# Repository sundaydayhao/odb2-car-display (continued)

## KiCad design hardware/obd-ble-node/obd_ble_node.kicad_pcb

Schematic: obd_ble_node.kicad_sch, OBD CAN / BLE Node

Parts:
AE1: AANI-CH-0133-Q; AANI-CH-0133-Q_Corner; MPN AANI-CH-0133-Q-T
C1: 2.2u 50V; C_0805_2012Metric; MPN GRM21BR71H225KA12L
C2: 100n 50V; C_0402_1005Metric; MPN GRM155R71H104KE14D
C3: 100n 16V; C_0402_1005Metric; MPN 100n 16V
C4, C5: 10u 25V; C_0805_2012Metric; MPN GRM21BR61E106KA73L
C6: 2.2u 10V; C_0402_1005Metric; MPN 2.2u 10V
C7, C11: 10u 10V; C_0603_1608Metric; MPN 10u 10V
C8, C9, C10, C12, C13, C14, C15, C22: 100n; C_0402_1005Metric; MPN 100n
C16, C17: 1u; C_0402_1005Metric; MPN 1u
C18, C19: 16p C0G; C_0402_1005Metric; MPN 16p C0G
C20, C21: 1.5p C0G; C_0201_0603Metric; MPN 1.5p C0G
C23: DNP / ANT TUNE; C_0402_1005Metric; MPN DNP / ANT TUNE; not fitted
D1: SS110 100V; D_SMA; MPN SS110
D2: SMBJ18A; D_SMB; MPN SMBJ18A
D3: PESD2CANFD24V-T; SOT-23; MPN PESD2CANFD24V-T
D4: GREEN; LED_0402_1005Metric; MPN GREEN
F1: 500mA 63V; Fuse_1206_3216Metric; MPN 0466.500NR
FB1: 600R@100M 500mA; L_0402_1005Metric; MPN BLM15AG601SN1D
H1: D1.2 NPTH; Fixture_Round_D1.2mm; MPN D1.2 NPTH
H2: 1.6x1.2 NPTH; Fixture_Slot_1.6x1.2mm; MPN 1.6x1.2 NPTH
J1: OBD-II 16P / STRAIGHT TAIL ASSUMPTION; OBD_StraightTail_16P_4x8p6_Assumed; MPN OBD-II 16P / STRAIGHT TAIL ASSUMPTION
L1: 10uH >=3A Isat; L_Coilcraft_XAL4030-XXX; MPN XGL4030-103MEC
L2: 2.4nH; L_0201_0603Metric; MPN LQP03TG2N4B02D
L3: 5.6nH TUNE; L_0402_1005Metric; MPN LQW15AN5N6C10
L4: 1.8nH TUNE; L_0402_1005Metric; MPN LQW15AN1N8C00
R1: 84.5k 1%; R_0402_1005Metric; MPN 84.5k 1%
R2: 16.2k 1%; R_0402_1005Metric; MPN 16.2k 1%
R3, R4, R5, R6, R7, R8: 10k; R_0402_1005Metric; MPN 10k
R9: 1M 1%; R_0402_1005Metric; MPN 1M 1%
R10: 100k 1%; R_0402_1005Metric; MPN 100k 1%
R11: 1k; R_0402_1005Metric; MPN 1k
R12: 499R; R_0402_1005Metric; MPN 499R
TP1: GND; TestPoint_Pad_D1.0mm; MPN GND
TP2: +3V3; TestPoint_Pad_D1.0mm; MPN +3V3
TP3: EN; TestPoint_Pad_D1.0mm; MPN EN
TP4: BOOT; TestPoint_Pad_D1.0mm; MPN BOOT
TP5: U0RX; TestPoint_Pad_D1.0mm; MPN U0RX
TP6: UART_TX; TestPoint_Pad_D1.0mm; MPN UART_TX
TP7: USB_DM; TestPoint_Pad_D1.0mm; MPN USB_DM
TP8: USB_DP; TestPoint_Pad_D1.0mm; MPN USB_DP
TP9: +5V; TestPoint_Pad_D1.0mm; MPN +5V
U1: LMR51610YDBVR; SOT-23-6; MPN LMR51610YDBVR
U2: TLV75533PDBVR; SOT-23-5; MPN TLV75533PDBVR
U3: TCAN1044AVDRBRQ1; VSON-8-1EP_3x3mm_P0.65mm_EP1.65x2.4mm; MPN TCAN1044AVDRBRQ1
U4: SN74LVC1G32DCKR; SOT-353_SC-70-5; MPN SN74LVC1G32DCKR
U5: ESP32-C3FH4X; QFN-32-1EP_5x5mm_P0.5mm_EP3.7x3.7mm; MPN ESP32-C3FH4X
Y1: 40MHz CL=10pF; Crystal_SMD_3225-4Pin_3.2x2.5mm; MPN ABM8G-40.000MHZ-10-D2X-T

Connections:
/+3V3: C7.1, C9.1, C10.1, C13.1, C14.1, C15.1, FB1.1, R3.1, R4.1, R5.1, R6.1, R7.1, R8.1, TP2.1, U2.5 (OUT), U3.5 (VIO), U4.5 (VCC), U5.11 (VDD3P3_RTC), U5.17 (VDD3P3_CPU), U5.31 (VDDA_1), U5.32 (VDDA_2)
/+5V: C4.1, C5.1, C6.1, C8.1, L1.2, R1.1, TP9.1, U2.1 (IN), U2.3 (EN), U3.3 (VCC)
/ANT_FEED: AE1.1 (RF_FEED), C23.1, L3.2
/BOOT: R8.2, TP4.1, U5.15 (GPIO9 / BOOT)
/BOOT_SW: C3.1, U1.1 (CB)
/CAN_H: D3.2 (CANH), J1.6 (OBD_6), U3.7 (CANH)
/CAN_L: D3.1 (CANL), J1.14 (OBD_14), U3.6 (CANL)
/CAN_RX: U3.4 (RXD), U5.8 (GPIO3 / CAN_RX)
/CAN_STB: R4.2, U3.8 (STB), U5.10 (GPIO5 / CAN_STB)
/CAN_TX: U4.1 (A), U5.5 (GPIO1 / CAN_TX)
/EN: C17.1, R5.2, TP3.1, U5.7 (CHIP_EN)
/FB5: R1.2, R2.1, U1.3 (FB)
/GND: C1.2, C2.2, C4.2, C5.2, C6.2, C7.2, C8.2, C9.2, C10.2, C11.2, C12.2, C13.2, C14.2, C15.2, C16.2, C17.2, C18.2, C19.2, C20.2, C21.2, C22.2, C23.2, D2.2 (A2), D3.3 (GND), D4.1 (K), J1.4 (OBD_4), J1.5 (OBD_5), L4.2, R2.2, R10.2, TP1.1, U1.2 (GND), U2.2 (GND), U3.2 (GND), U3.9 (EP), U4.3 (GND), U5.33 (EP_GND), Y1.2 (G), Y1.4 (G)
/LED: R11.1, U5.12 (GPIO6 / LED)
/LED_A: D4.2 (A), R11.2
/RF50: C21.1, L2.2, L3.1, L4.1
/RF_SOC: C20.1, L2.1, U5.1 (LNA_IN)
/STRAP2: R6.2, U5.6 (GPIO2 / STRAP)
/STRAP8: R7.2, U5.14 (GPIO8 / STRAP)
/SW: C3.2, L1.1, U1.6 (SW)
/TXD_GATE: U3.1 (TXD), U4.4 (Y)
/TX_INHIBIT: R3.2, U4.2 (B), U5.9 (GPIO4 / TX_INHIBIT)
/U0RX: TP5.1, U5.27 (GPIO20 / U0RXD)
/U0TX: R12.1, U5.28 (GPIO21 / U0TXD)
/UART_TX: R12.2, TP6.1
/USB_DM: TP7.1, U5.25 (GPIO18 / USB_D-)
/USB_DP: TP8.1, U5.26 (GPIO19 / USB_D+)
/VBAT: F1.1, J1.16 (OBD_16)
/VBAT_ADC: C22.1, R9.2, R10.1, U5.4 (GPIO0 / ADC1_CH0)
/VBAT_FUSED: D1.2 (A), F1.2
/VDD_RF: C11.1, C12.1, FB1.2, U5.2 (VDD3P3_1), U5.3 (VDD3P3_2)
/VDD_SPI: C16.1, U5.18 (VDD_SPI)
/VIN_PROT: C1.1, C2.1, D1.1 (K), D2.1 (A1), R9.1, U1.4 (EN), U1.5 (VIN)
/XTAL_N: C19.1, U5.29 (XTAL_N), Y1.3
/XTAL_P: C18.1, U5.30 (XTAL_P), Y1.1

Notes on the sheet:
REV A3 / 38.5 x 16.6 mm / CAN + BLE / GROUPED TEST PADS + FIXTURE DATUMS
J1: straight-tail 4.00 x 8.60 mm grid ASSUMED Plated slot 2.40 x 1.20 mm: verify actual plug fit.
12 V INPUT / REVERSE PROTECTION / 65 V BUCK / 5 V -> 3.3 V
No 120 ohm termination on vehicle stub. TX inhibit HIGH physically forces recessive.
RESET / STRAPS / 40 MHz
C3FH4X: integrated flash, pins 19..24 NC. VDD_SPI is a supply output.
RF / 50 ohm reference plane / match values require VNA tuning in final case
ADC senses VIN_PROT; fuse and diode drop are not compensated.
USB pads: DATA ONLY. Fixture power requires vehicle disconnection.

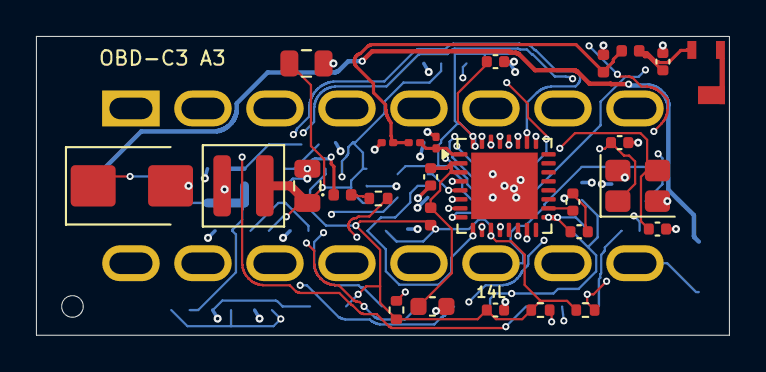
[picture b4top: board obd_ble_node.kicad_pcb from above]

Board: 4 copper layers, 38.5 x 16.6 mm, 64 parts (34 on the bottom side), 35 nets.

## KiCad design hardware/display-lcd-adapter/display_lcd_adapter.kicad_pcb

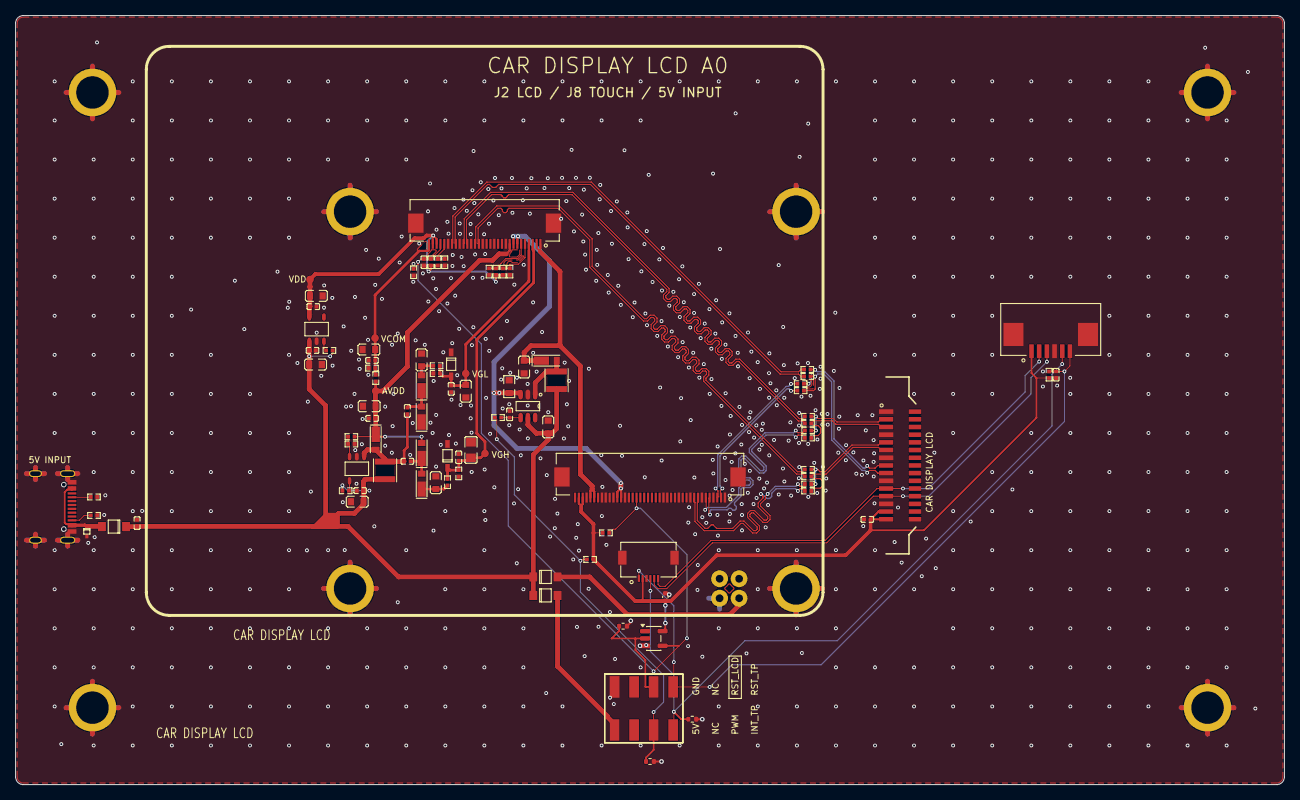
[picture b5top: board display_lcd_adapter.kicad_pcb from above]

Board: 2 copper layers, 165.0 x 100.0 mm, 108 parts (0 on the bottom side), 53 nets.

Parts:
C1: 1u / 16V; C0402__b328da3f93
C2: 1u/16V; C0402__b328da3f93
C3, C8, C9, C11, C13, C15, C16, C22, C24, C25, C26: 0.1u/50V; C0402__b328da3f93
C4, C5, C7, C10, C12, C14, C21, C27: 10u/25V; C0603__4affcd651d
C6: 22p/50V; C0402__b328da3f93
C17, C18: 1u/50V; C0603__4affcd651d
C23: 10u/50V; C0805__9959ce48b0
C28: 100n / 16V; C_0402_1005Metric__56c42d4718
D1, D3, D12: DSS24; SOD123FL__46ae4cb21a
D2: LESD5D5.0CT1G; SOD523__04fef8a58b
D4, D5, D6, D7, D8, D9: LMBR140ET1G; SOD323HE__f9a9ee848d
D10: LMSZ5233BT1G; SOD123__b888afbd6d
D11: MM1W18; SOD123__b888afbd6d
H1, H2, H3, H4, H5, H6, H7, H8: STD; HOLE6P2_4P22__65e4372978
J1: USB_TYPEC_16P_F; USB_TYPEC_16P_F__86066a2b25
J2: LCD_30P_0.5mm; FFC30P_0P5__db095f96ca
J3: DSI_15P_1mm; FFC_15P_1_MIPI__6610367bd7
J5: FPC_6P_1mm_UNUSED; FFC6P_1_UP__634cfe9cbb
J6: AUX_5V_BL_RESET_TOUCH; CON4X2_2P54_SMT__7e2a9205d1
J7: FPC_40P_UNUSED; FFC40P_0P5__8d5a270b71
J8: GT911_6P_0.5mm; FFC6P_0P5_UP__fd49314884
L1, L2: 10uH_0.8A; L3012S__5941442135
R1, R2, R3, R4, R5, R6, R7, R10, R11, R13, R14, R24, R38: 10k; R0402__b308b0f41e
R8, R9: 5.1k; R0402__b308b0f41e
R12: 1.1; R0603__10d1fcc181
R15: 22k; R0402__b308b0f41e
R16: 3.3k; R0402__b308b0f41e
R17, R18: 220; R0402__b308b0f41e
R19, R20: 51k; R0402__b308b0f41e
R22, R37: 1k; R0402__b308b0f41e
R23: 2k; R0402__b308b0f41e
R25, R26, R27, R28, R29, R30: 0; R0402__b308b0f41e
R31, R32, R33, R34, R35, R36: 0R; R0402__b308b0f41e
R39, R41: 10k; R_0402_1005Metric__e20e110129
R40: 100k; R_0402_1005Metric__e20e110129
TP1, TP2, TP3, TP4: TEST; TPC1__3c95fc0e3d
TP5: TEST; TPC1__999ff27256
TP6, TP7, TP8, TP9: TEST; HOLE2P2_1__191d9da361
U1: ETA1611; SOT23-6__2edaa2116b
U2: ME6211C18M5G-N; SOT23-5__5f716075cd
U3: AP3012k; SOT23-5__5f716075cd
U4: SN74LVC1G07DBVR; SOT-23-5__81a06d98de

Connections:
A_CLKN: J2.18, R27.1
A_CLKP: J2.17, R28.1
A_DATN0: J2.24, R29.1
A_DATN1: J2.21, R25.1
A_DATP0: J2.23, R30.1
A_DATP1: J2.20, R26.1
B_CLKN: J7.9, R33.1
B_CLKP: J7.8, R34.1
B_DATN0: J7.3, R35.1
B_DATN1: J7.6, R31.1
B_DATP0: J7.2, R36.1
B_DATP1: J7.5, R32.1
ESP32_CLKN: J3.5, R27.2, R33.2
ESP32_CLKP: J3.6, R28.2, R34.2
ESP32_DATN0: J3.8, R29.2, R35.2
ESP32_DATN1: J3.2, R25.2, R31.2
ESP32_DATP0: J3.9, R30.2, R36.2
ESP32_DATP1: J3.3, R26.2, R32.2
ESP32_I2C_SCL: J3.11, J5.2, J8.6
ESP32_I2C_SDA: J3.12, J5.3, J8.5
GND: C1.2, C2.2, C3.2, C4.2, C5.2, C6.2, C7.2, C8.2, C9.2, C10.2, C11.2, C12.2, C13.2, C14.2, C17.2, C18.2, C21.2, C22.2, C23.2, C24.2, C25.2, C26.2, C27.2, C28.2, D2.1, D8.2, D10.2, D11.1, H1.1, H2.1, H3.1, H4.1, H5.1, H6.1, H7.1, H8.1, J1.1, J1.2, J1.15, J1.16, J1.17, J1.18, J1.19, J1.20, J2.10, J2.13, J2.16, J2.19, J2.22, J2.25, J2.31, J2.32, J3.1, J3.4, J3.7, J3.10, J3.13, J5.4, J5.7, J5.8, J6.2, J7.1, J7.4, J7.7, J7.10, J7.13, J7.16, J7.17, J7.27, J7.30, J7.32, J7.33, J7.37, J7.41, J7.42, J8.3, J8.7, J8.8, R5.1, R6.1, R7.1, R8.1, R9.1, R12.1, R16.2, R19.1, R20.1, R22.1, R38.1, R39.2, R40.2, R41.2, TP7.1, U1.2, U2.2, U3.2, U4.3
INT_TP: J5.5, J6.7, J8.4, R40.1
LCD_AVDD: C13.1, C14.1, D5.2, D6.1, J2.9, R15.1, R23.2, TP4.1
LCD_RESET_HOST: J6.6, R39.1, U4.2
LCD_VCOM: C26.1, C27.1, J2.30, R22.2, R23.1, TP3.1
LCD_VDD: C9.1, C10.1, J2.28, J2.29, R1.2, R2.2, R3.2, R4.2, TP5.1, U2.5
LCD_VGH: C23.1, C24.1, D11.2, J2.3, R18.2, R20.2, TP2.1
LCD_VGL: C21.1, C22.1, D10.1, J2.4, R17.2, R19.2, TP1.1
LED+: C5.1, D4.2, J2.1, J2.2, J7.35, J7.36
LED-: J2.7, J2.8, J7.28, J7.29, R12.2, U1.3
LED_CTRL: J6.5, R11.2, R24.1, R41.1
N17127832: D4.1, L1.2, U1.1
N17127878: C6.1, R11.1, U1.4
N17128822: R13.1, U2.3
N17131715: J1.6, R8.2
N17131721: J1.12, R9.2
N17132617: D3.1, J6.1
N17134769: R14.1, U3.4
N17134948: C15.2, C16.2, D5.1, L2.2, U3.1
N17135258: R15.2, R16.1, U3.3
N17135942: C16.1, D8.1, D9.2
N17136021: C15.1, D6.2, D7.1
N17136250: C18.1, D7.2, R18.1
N17136498: C17.1, D9.1, R17.1
N17147084: D12.1, TP6.1
RESET_LCD: C1.1, J2.27, J7.24, R4.1, R37.1, R38.2, U4.4
RESET_TP: C2.1, J5.6, J6.8, J8.1, R10.1
SHLR: J2.6, R2.1, R6.2
STBYB: J2.26, R3.1, R7.2
UPDN: J2.5, R1.1, R5.2
USB_5V: D1.1, D2.2, J1.3, J1.4, J1.13, J1.14
VCC_5V: C4.1, C7.1, C8.1, C11.1, C12.1, C25.1, D1.2, D3.2, D12.2, L1.1, L2.1, R13.2, R14.2, U1.5, U2.1, U3.5
VDD_3V3: C3.1, C28.1, J3.14, J3.15, J5.1, J7.38, J7.39, J8.2, R10.2, R24.2, R37.2, U4.5

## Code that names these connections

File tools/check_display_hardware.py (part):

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    if key not in expected or key not in actual or expected.get(key)!=actual.get(key):errors.append(['SCH/PCB mismatch',key,expected.get(key,'MISSING'),actual.get(key,'MISSING')])
duplicates=[ref for ref,n in collections.Counter(refs).items() if n!=1]
required={('J302','17'):'DSI_A_CLKP',('J302','18'):'DSI_A_CLKN',('J302','20'):'DSI_A_DATA1P',('J302','21'):'DSI_A_DATA1N',('J302','23'):'DSI_A_DATA0P',('J302','24'):'DSI_A_DATA0N',
          ('J302','27'):'PANEL_RESET_LCD',('J302','28'):'PANEL_LCD_VDD',('U304','2'):'CNN_GPIO27',('U304','4'):'PANEL_RESET_LCD',('U304','5'):'ESP_3V3',
          ('J308','1'):'CNN_GPIO23',('J308','2'):'ESP_3V3',('J308','3'):'GND',('J308','4'):'CNN_GPIO22',('J308','5'):'N18412242',('J308','6'):'N18412230',('R341','1'):'CNN_GPIO26',('R341','2'):'GND'}
# These parts originally shared the Ethernet sheet but are essential to Wi-Fi / SD.
required.update({('Q8','1'):'SD_PWRN',('Q8','2'):'ESP_3V3',('Q8','3'):'SD1_VDD',
                 ('R229','1'):'GND',('R229','2'):'SD_PWRN',('R231','2'):'SD_PWRN',
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                 ('U401','5'):'GND',('U401','6'):'PWR_RISE_CT',('U401','7'):'VCC_5V',('U401','8'):'VCC_5V',('U401','9'):'GND',
                 ('J19','3'):'USB_DBG_5V',('J19','7'):'USB1P1_N',('J19','8'):'USB1P1_P',
                 ('J19','9'):'USB1P1_N',('J19','10'):'USB1P1_P',
                 ('R104','1'):'GPIO24',('R104','2'):'USB1P1_N',('R105','1'):'GPIO25',('R105','2'):'USB1P1_P',
                 ('Q4','2'):'INPUT_5V',('Q4','3'):'USB_DBG_5V',('Q7','2'):'INPUT_5V',('Q7','3'):'VIN_5V',
                 ('R234','1'):'USB_DP',('R234','2'):'GND',('U4','52'):'GPIO24',('U4','53'):'GPIO25',
                 ('R209','1'):'GPIO36_BOOTMODE',('R209','2'):'ESP_3V3',
                 ('R204','1'):'GPIO36',('R204','2'):'GPIO36_BOOTMODE'})
# Keep the P4X core supply connection and compensation while removing the
# external USB host branch; pin 54 is not a spare on this silicon revision.
required.update({('U4','54'):'N18792940',('R232','1'):'N18792940',('R232','2'):'ESP_VDD_HP',
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    ('R432','1'):'BAT_5V',('R432','2'):'BOOST_FB',('R433','1'):'BOOST_FB',('R433','2'):'GND',
    ('Q10','1'):'POWER_OR_GATE',('Q10','2'):'BAT_5V',('Q10','3'):'INPUT_5V',
    ('Q11','1'):'POWER_OR_GATE',('Q11','2'):'USB_DBG_5V',('Q11','3'):'INPUT_5V'})
for number,net in enumerate(['GND','VIN_5V','ESP_3V3','GPIO37','GPIO38','ESP_EN','GPIO35_BOOTMODE'],401):
    required[(f'TP{number}','1')]=net
if a7:
    required={key:value for key,value in required.items() if key[0] not in removed_otg_refs}
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if enclosure.get('revision','').startswith('A7'):
    # The mechanical redesign must retain the analog mic bias and active-low
    # recovery buttons.  A connector footprint swap is not a pin-number swap.
    enclosure_pins={('J7','1'):'MICP',('J7','2'):'N18300564',
                    ('R66','2'):'GND',
                    ('J16','1'):'N18423897',('J16','2'):'N18423915',
                    ('SW1','1'):'GND',('SW1','2'):'ESP_EN',('SW1','MP'):'GND',
                    ('SW2','1'):'GND',('SW2','2'):'GPIO35_BOOTMODE',('SW2','MP'):'GND'}
    for key,value in enclosure_pins.items():
        if expected.get(key)!=value:errors.append(['enclosure interface pin changed',key,expected.get(key),value])
    for ref in ('SW1','SW2'):
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    elif len({f.m_Uuid.AsString() for f in fp.GetFields()})!=len(list(fp.GetFields())):
        errors.append(['duplicate footprint field UUID',ref])
if 'R209' in fpmap and (fpmap['R209'].IsDNP() or fpmap['R209'].GetValue() not in ['10K','10k','10kR']):
    errors.append(['GPIO36 download strap requires fitted 10k pull-up'])
lcd=fpmap['J302'];box=b.GetBoardEdgesBoundingBox()
profile_path=a.project/'panel-profile.json'
panel_profile=json.loads(profile_path.read_text(encoding='utf-8')) if profile_path.exists() else None
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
